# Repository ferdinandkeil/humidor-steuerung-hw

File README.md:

# Humidor Steuerung (Hardware)

Die aktuelle Version der Steuerung ist v35. Gefertigt wurden nur v31 und v35.

Wenn nicht anders angegeben stehen die Dateien unter der TAPR Open Hardware License (siehe LICENSE).

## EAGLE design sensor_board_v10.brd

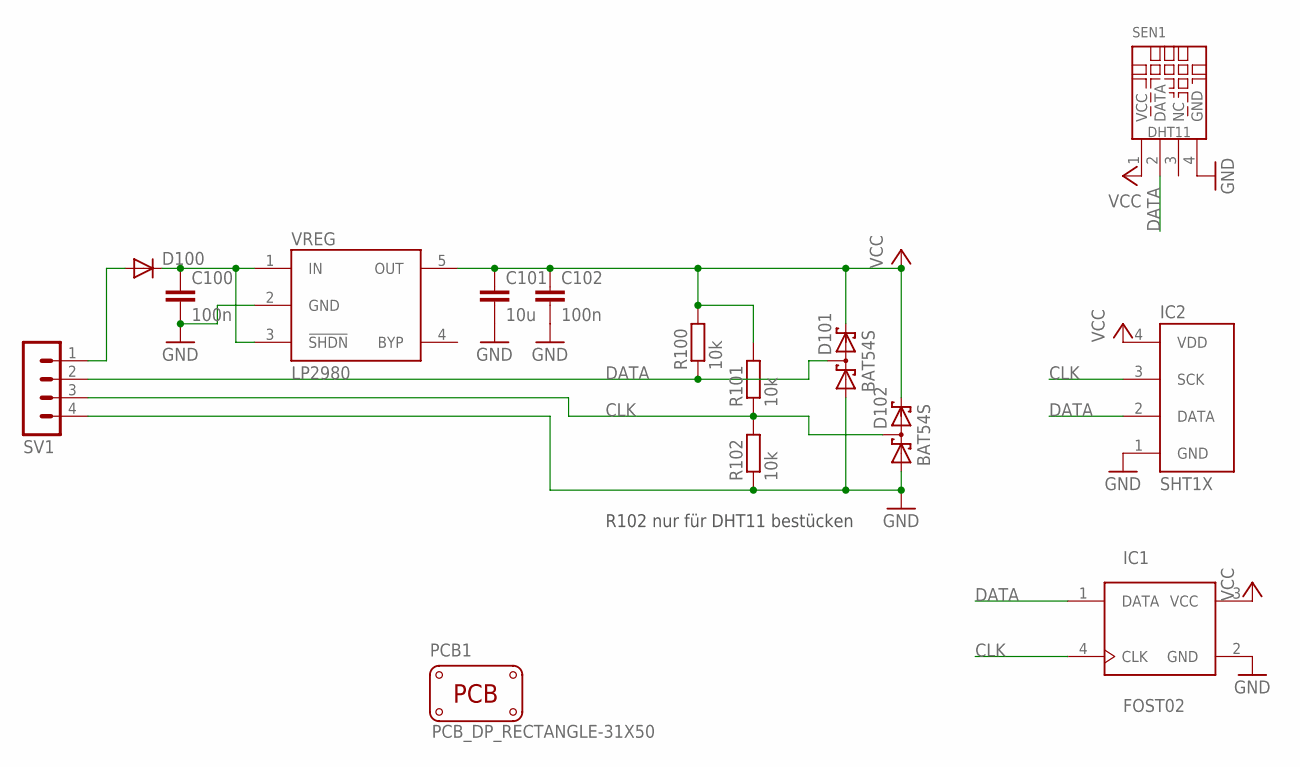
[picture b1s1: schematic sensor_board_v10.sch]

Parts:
C100, C102: 100n; C0805
C101: 10u; C0805
D100: DIODE-SOD123; SOD123
D101, D102: BAT54S; SOT23
IC1: FOST02
IC2: SHT1X
PCB1: PCB_DP_RECTANGLE-31X50; DP5031_V1
R100, R101, R102: 10k; R0805
SEN1: DHT11
SV1: MA04-1
VREG: LP2980; SOT-23-5

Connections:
CLK: D102.3 (C1A2), IC1.4 (CLK), IC2.3 (SCK), R101.1, R102.2, SV1.3
DATA: D101.3 (C1A2), IC1.1 (DATA), IC2.2 (DATA), R100.1, SEN1.2 (DATA), SV1.2
GND: C100.2, C101.2, C102.2, D101.1 (A1), D102.1 (A1), IC1.2 (GND), IC2.1 (GND), R102.1, SEN1.4 (GND), SV1.4, VREG.2 (GND)
unnamed: C100.1, D100.C, VREG.1 (IN), VREG.3 (!SHDN)
unnamed: D100.A, SV1.1
VCC: C101.1, C102.1, D101.2 (C2), D102.2 (C2), IC1.3 (VCC), IC2.4 (VDD), R100.2, R101.2, SEN1.1 (VCC), VREG.5 (OUT)

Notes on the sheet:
R102 nur für DHT11 bestücken

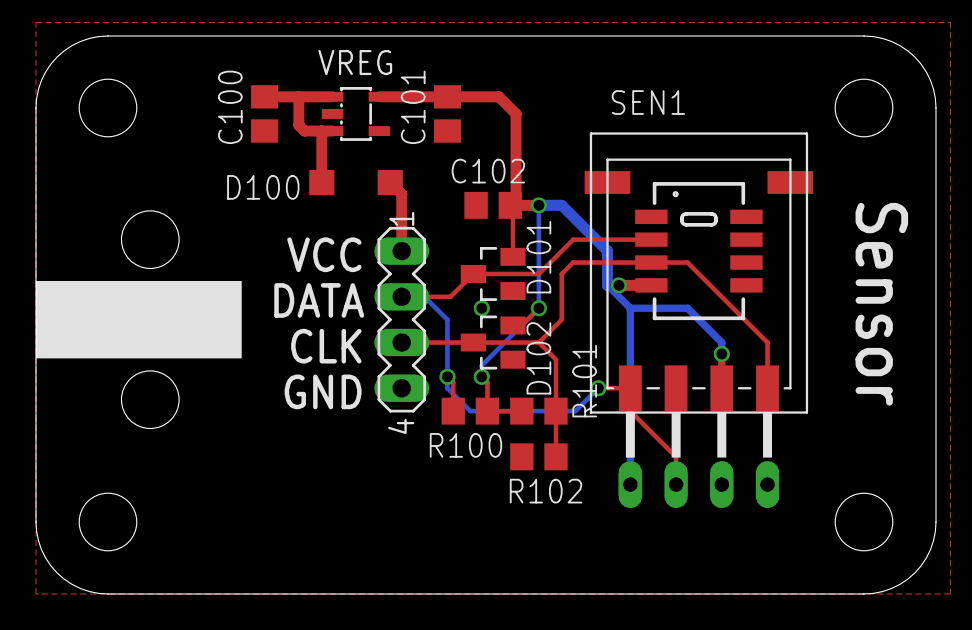
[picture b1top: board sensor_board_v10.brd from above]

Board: 2 copper layers, 50.0 x 31.0 mm, 16 parts (1 on the bottom side), 6 nets.

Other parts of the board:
U$1: ICON_LOGO_HUMI_CONTR

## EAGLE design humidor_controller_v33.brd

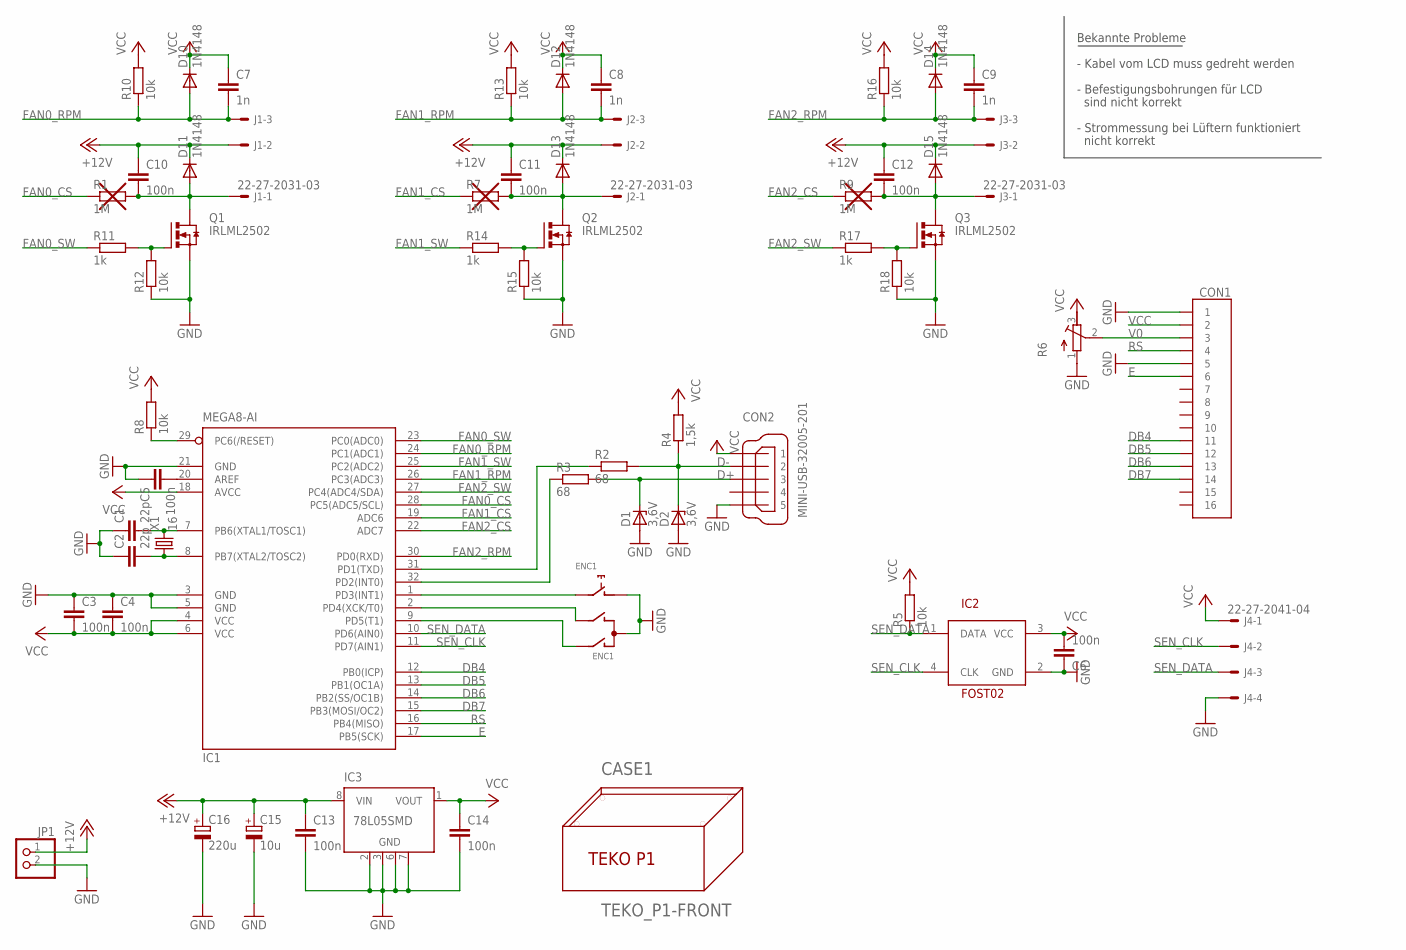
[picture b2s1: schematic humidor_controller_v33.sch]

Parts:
C1, C2: 22p; C0805
C3, C4, C5, C6, C10, C11, C12, C13, C14: 100n; C0805
C7, C8, C9: 1n; C0805
C15: 10u; PANASONIC_D
C16: 220u; PANASONIC_G
CASE1: TEKO_P1-FRONT; TEKO_P1_FRONT
CON1: 52207-16
CON2: MINI-USB-32005-201; 32005-201
D1, D2: 3,6V; SOD80C
D10, D11, D12, D13, D14, D15: 1N4148; SOD323-R
ENC1: NOBLE_RE0124; RE0124
IC1: MEGA8-AI; TQFP32-08
IC2: FOST02
IC3: 78L05SMD; SO08
J1, J2, J3: 22-27-2031-03; 6410-03
J4: 22-27-2041-04; 6410-04
JP1: PINHD-1X2; 1X02
Q1, Q2, Q3: IRLML2502; SOT23
R1, R7, R9: 1M; R0805
R2, R3: 68; R0805
R4: 1,5k; R0805
R5, R8, R10, R12, R13, R15, R16, R18: 10k; R0805
R6: R-TRIMM4G/J; RTRIM4G/J
R11, R14, R17: 1k; R0805
X1: 16; HC49UP

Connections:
+12V: C10.1, C11.1, C12.1, C13.1, C15.+, C16.+, D11.C, D13.C, D15.C, IC3.8 (VIN), J1.2, J2.2, J3.2, JP1.1
D+: CON2.3, D1.C, R3.2
D-: CON2.2, D2.C, R2.2, R4.1
DB4: CON1.11, IC1.12 (PB0(ICP))
DB5: CON1.12, IC1.13 (PB1(OC1A))
DB6: CON1.13, IC1.14 (PB2(SS/OC1B))
DB7: CON1.14, IC1.15 (PB3(MOSI/OC2))
E: CON1.6, IC1.17 (PB5(SCK))
FAN0_CS: IC1.28 (PC5(ADC5/SCL)), R1.1
FAN0_CS_: C10.2, D11.A, J1.1, Q1.3 (D), R1.2
FAN0_RPM: C7.2, D10.A, IC1.24 (PC1(ADC1)), J1.3, R10.1
FAN0_SW: IC1.23 (PC0(ADC0)), R11.1
FAN1_CS: IC1.19 (ADC6), R7.1
FAN1_CS_: C11.2, D13.A, J2.1, Q2.3 (D), R7.2
FAN1_RPM: C8.2, D12.A, IC1.26 (PC3(ADC3)), J2.3, R13.1
FAN1_SW: IC1.25 (PC2(ADC2)), R14.1
FAN2_CS: IC1.22 (ADC7), R9.1
FAN2_CS_: C12.2, D15.A, J3.1, Q3.3 (D), R9.2
FAN2_RPM: C9.2, D14.A, IC1.30 (PD0(RXD)), J3.3, R16.1
FAN2_SW: IC1.27 (PC4(ADC4/SDA)), R17.1
GND: C1.1, C2.1, C3.1, C4.1, C5.1, C6.1, C13.2, C14.2, C15.-, C16.-, CON1.1, CON1.5, CON2.5, D1.A, D2.A, ENC1.+ (1), ENC1.C, IC1.3 (GND), IC1.5 (GND), IC1.21 (GND), IC2.2 (GND), IC3.2 (GND), IC3.3 (GND), IC3.6 (GND), IC3.7 (GND), J4.4, JP1.2, Q1.2 (S), Q2.2 (S), Q3.2 (S), R6.1 (E), R12.1, R15.1, R18.1
unnamed: IC1.29 (PC6(/RESET)), R8.1
unnamed: C2.2, IC1.8 (PB7(XTAL2/TOSC2)), X1.1
unnamed: C1.2, IC1.7 (PB6(XTAL1/TOSC1)), X1.2
unnamed: Q2.1 (G), R14.2, R15.2
unnamed: Q3.1 (G), R17.2, R18.2
unnamed: C5.2, IC1.20 (AREF)
unnamed: Q1.1 (G), R11.2, R12.2
unnamed: IC1.31 (PD1(TXD)), R2.1
unnamed: ENC1.- (2), IC1.1 (PD3(INT1))
unnamed: ENC1.B, IC1.2 (PD4(XCK/T0))
unnamed: ENC1.A, IC1.9 (PD5(T1))
unnamed: IC1.32 (PD2(INT0)), R3.1
RS: CON1.4, IC1.16 (PB4(MISO))
SEN_CLK: IC1.11 (PD7(AIN1)), IC2.4 (CLK), J4.2
SEN_DATA: IC1.10 (PD6(AIN0)), IC2.1 (DATA), J4.3, R5.1
V0: CON1.3, R6.2 (S)
VCC: C3.2, C4.2, C6.2, C7.1, C8.1, C9.1, C14.1, CON1.2, CON2.1, D10.C, D12.C, D14.C, IC1.4 (VCC), IC1.6 (VCC), IC1.18 (AVCC), IC2.3 (VCC), IC3.1 (VOUT), J4.1, R4.2, R5.2, R6.3 (A), R8.2, R10.2, R13.2, R16.2

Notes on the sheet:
Bekannte Probleme
- Kabel vom LCD muss gedreht werden
- Befestigungsbohrungen für LCD
sind nicht korrekt
- Strommessung bei Lüftern funktioniert
nicht korrekt

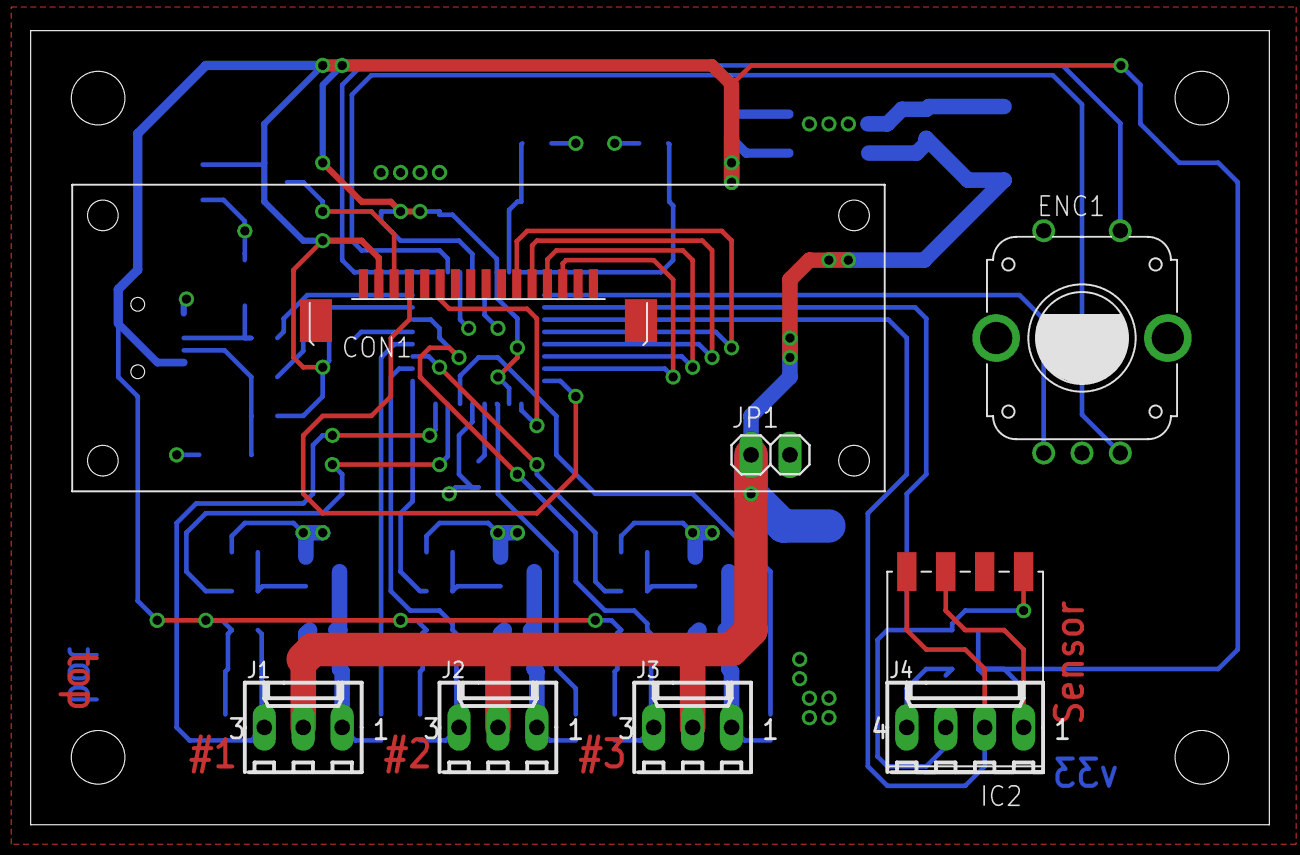
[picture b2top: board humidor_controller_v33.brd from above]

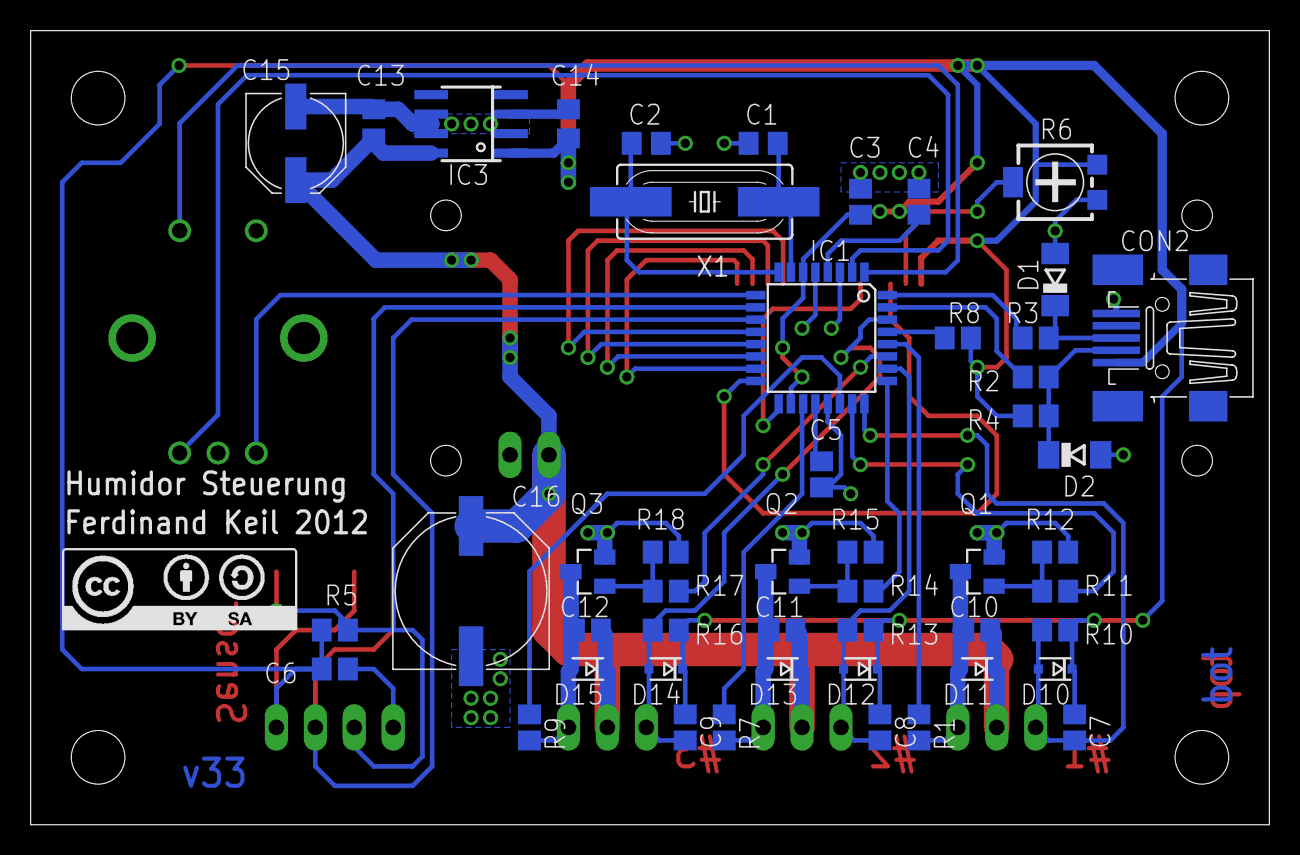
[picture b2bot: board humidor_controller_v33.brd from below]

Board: 2 copper layers, 80.8 x 51.8 mm, 60 parts (50 on the bottom side), 38 nets.

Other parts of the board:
U$1: LCD_HMC16223SG
U$2: CC-BY-SA

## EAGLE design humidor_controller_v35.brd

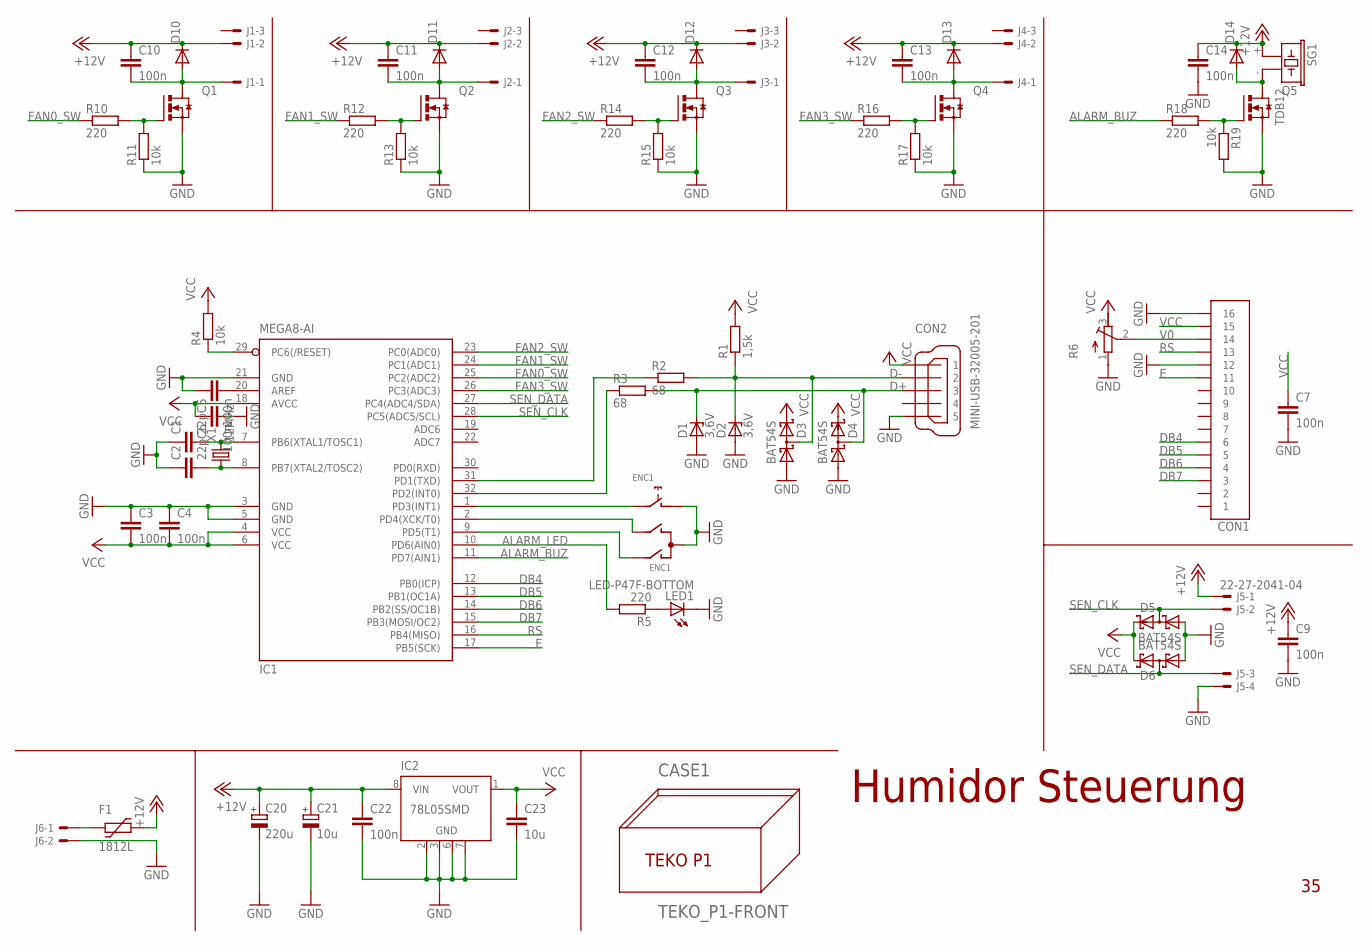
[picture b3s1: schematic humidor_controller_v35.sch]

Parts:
C1, C2: 22p; C0805
C3, C4, C5, C6, C7, C9, C10, C11, C12, C13, C14, C22: 100n; C0805
C20: 220u; PANASONIC_G
C21: 10u; PANASONIC_B
C23: 10u; C0805
CASE1: TEKO_P1-FRONT; TEKO_P1_FRONT
CON1: 52207-16
CON2: MINI-USB-32005-201; 32005-201
D1, D2: 3,6V; SOD80C
D3, D4, D5, D6: BAT54S; SOT23
D10, D11, D12, D13, D14: DIODE-SOD123; SOD123
ENC1: NOBLE_RE0124; RE0124
F1: 1812L
IC1: MEGA8-AI; TQFP32-08
IC2: 78L05SMD; SO08
J1, J2, J3, J4: 22-27-2031-03; 6410-03
J5: 22-27-2041-04; 6410-04
J6: 22-27-2021-02; 6410-02
LED1: LED-P47F-BOTTOM; P47F-BOTTOM
Q1, Q2, Q3, Q4, Q5: N-HEXFET_SOT23-IRLML2502; SOT23
R1: 1,5k; R0805
R2, R3: 68; R0805
R4, R11, R13, R15, R17, R19: 10k; R0805
R5, R10, R12, R14, R16, R18: 220; R0805
R6: R-TRIMM4G/J; RTRIM4G/J
SG1: TDB12; TDB
X1: 12MHz; HC49UP

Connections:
+12V: C9.1, C10.1, C11.1, C12.1, C13.1, C14.1, C20.+, C21.+, C22.1, D10.C, D11.C, D12.C, D13.C, D14.C, F1.P$2 (2), IC2.8 (VIN), J1.2, J2.2, J3.2, J4.2, J5.1, SG1.+ (1)
ALARM_BUZ: IC1.11 (PD7(AIN1)), R18.1
ALARM_LED: IC1.10 (PD6(AIN0)), R5.2
D+: CON2.3, D1.C, D4.3 (C1A2), R3.2
D-: CON2.2, D2.C, D3.3 (C1A2), R1.1, R2.2
DB4: CON1.6, IC1.12 (PB0(ICP))
DB5: CON1.5, IC1.13 (PB1(OC1A))
DB6: CON1.4, IC1.14 (PB2(SS/OC1B))
DB7: CON1.3, IC1.15 (PB3(MOSI/OC2))
E: CON1.11, IC1.17 (PB5(SCK))
FAN0_CS: C10.2, D10.A, J1.1, Q1.3 (D)
FAN0_SW: IC1.25 (PC2(ADC2)), R10.1
FAN1_CS: C11.2, D11.A, J2.1, Q2.3 (D)
FAN1_SW: IC1.24 (PC1(ADC1)), R12.1
FAN2_CS: C12.2, D12.A, J3.1, Q3.3 (D)
FAN2_CS1: C13.2, D13.A, J4.1, Q4.3 (D)
FAN2_SW: IC1.23 (PC0(ADC0)), R14.1
FAN3_SW: IC1.26 (PC3(ADC3)), R16.1
GND: C1.1, C2.1, C3.1, C4.1, C5.1, C6.2, C7.2, C9.2, C14.2, C20.-, C21.-, C22.2, C23.2, CON1.12, CON1.16, CON2.5, D1.A, D2.A, D3.1 (A1), D4.1 (A1), D5.1 (A1), D6.1 (A1), ENC1.+ (1), ENC1.C, IC1.3 (GND), IC1.5 (GND), IC1.21 (GND), IC2.2 (GND), IC2.3 (GND), IC2.6 (GND), IC2.7 (GND), J5.4, J6.2, LED1.C, Q1.2 (S), Q2.2 (S), Q3.2 (S), Q4.2 (S), Q5.2 (S), R6.1 (E), R11.1, R13.1, R15.1, R17.1, R19.2
unnamed: IC1.29 (PC6(/RESET)), R4.1
unnamed: C2.2, IC1.8 (PB7(XTAL2/TOSC2)), X1.1
unnamed: C1.2, IC1.7 (PB6(XTAL1/TOSC1)), X1.2
unnamed: Q2.1 (G), R12.2, R13.2
unnamed: Q3.1 (G), R14.2, R15.2
unnamed: Q4.1 (G), R16.2, R17.2
unnamed: C5.2, IC1.20 (AREF)
unnamed: LED1.A, R5.1
unnamed: Q1.1 (G), R10.2, R11.2
unnamed: IC1.31 (PD1(TXD)), R2.1
unnamed: F1.P$1 (1), J6.1
unnamed: ENC1.- (2), IC1.1 (PD3(INT1))
unnamed: ENC1.B, IC1.2 (PD4(XCK/T0))
unnamed: ENC1.A, IC1.9 (PD5(T1))
unnamed: IC1.32 (PD2(INT0)), R3.1
unnamed: D14.A, Q5.3 (D), SG1.- (2)
unnamed: Q5.1 (G), R18.2, R19.1
RS: CON1.13, IC1.16 (PB4(MISO))
SEN_CLK: D5.3 (C1A2), IC1.28 (PC5(ADC5/SCL)), J5.2
SEN_DATA: D6.3 (C1A2), IC1.27 (PC4(ADC4/SDA)), J5.3
V0: CON1.14, R6.2 (S)
VCC: C3.2, C4.2, C6.1, C7.1, C23.1, CON1.15, CON2.1, D3.2 (C2), D4.2 (C2), D5.2 (C2), D6.2 (C2), IC1.4 (VCC), IC1.6 (VCC), IC1.18 (AVCC), IC2.1 (VOUT), R1.2, R4.2, R6.3 (A)

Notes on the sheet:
Humidor Steuerung

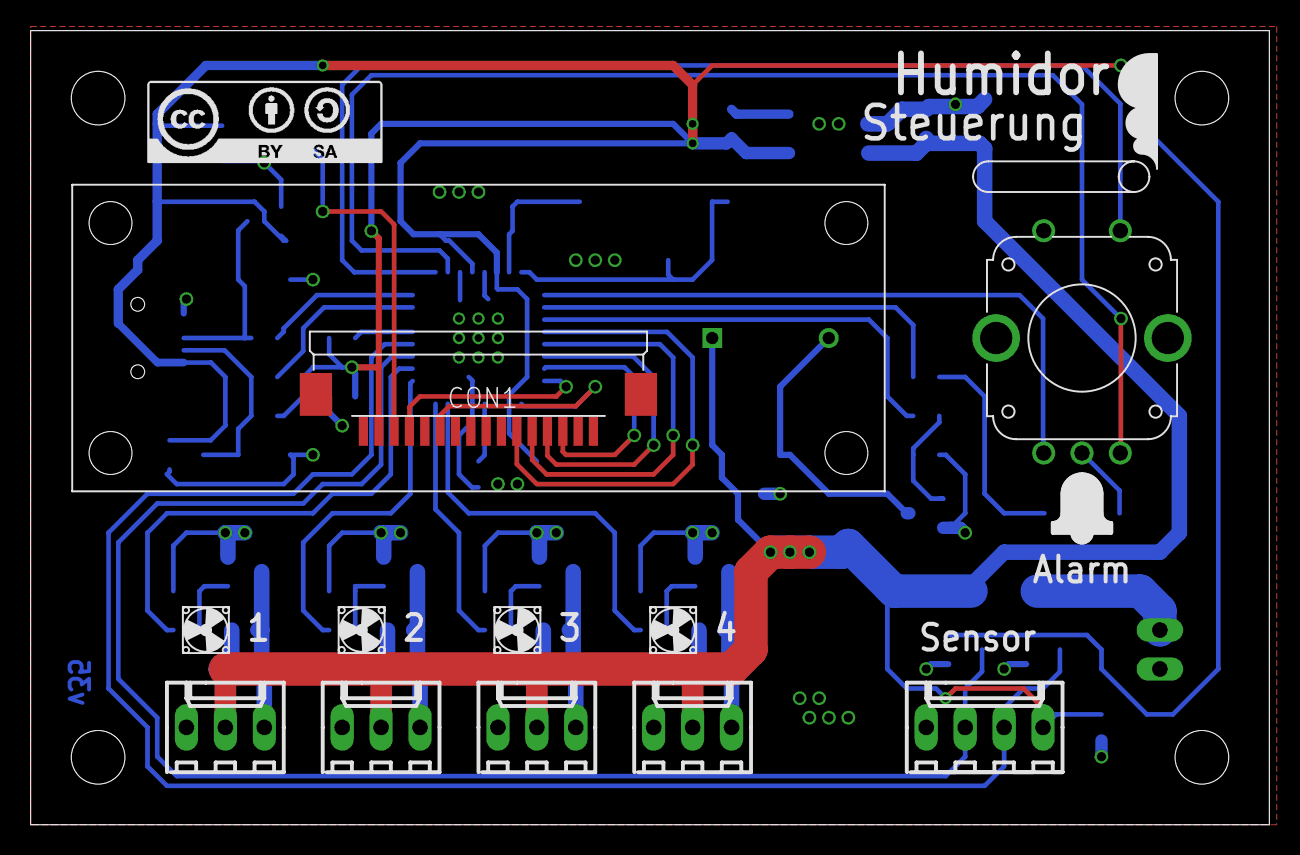
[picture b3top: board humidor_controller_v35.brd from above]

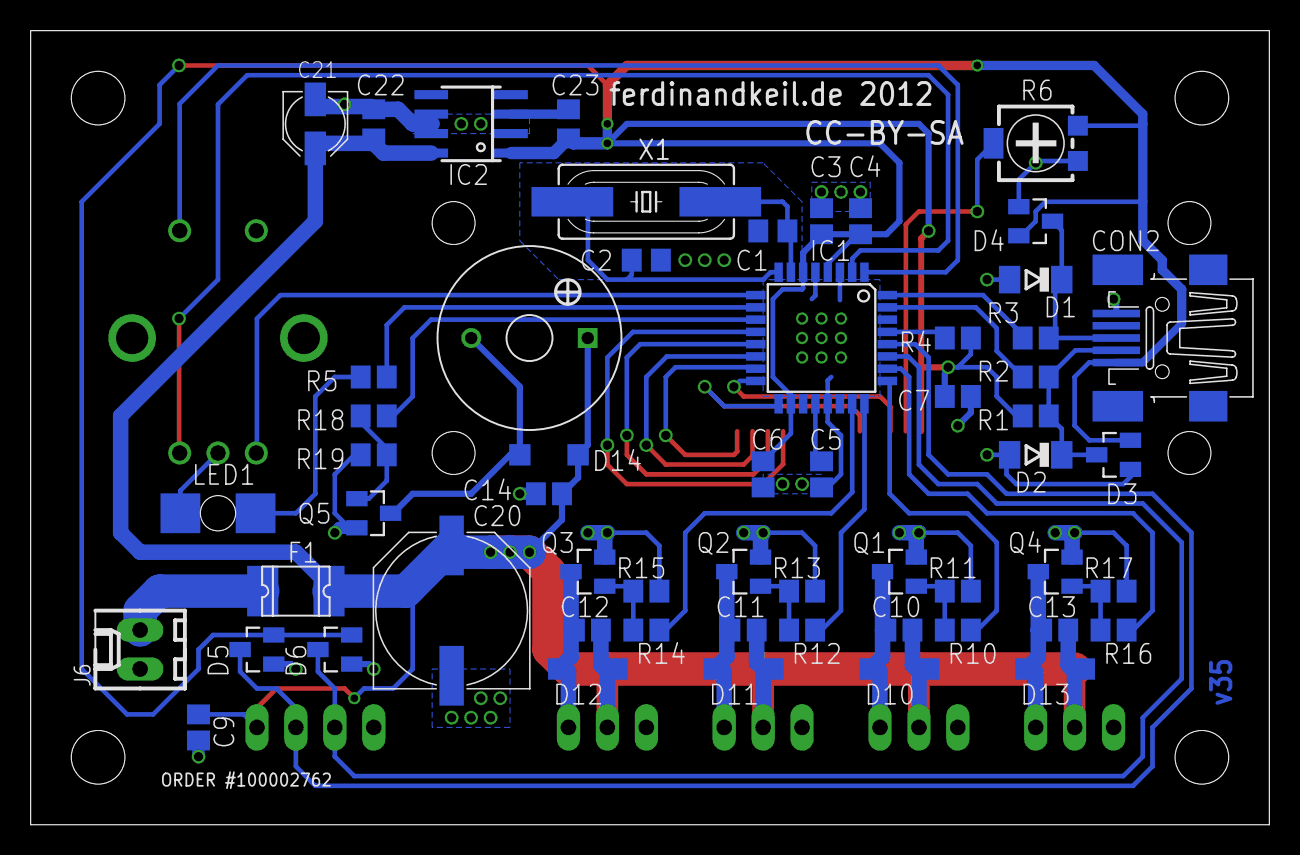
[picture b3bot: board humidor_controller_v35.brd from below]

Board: 2 copper layers, 80.8 x 51.8 mm, 72 parts (57 on the bottom side), 41 nets.

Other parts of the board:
U$1: LCD_HMC16223SG
U$2: CC-BY-SA
U$3: ICON_LOGO_HUMI_CONTR
U$4, U$5, U$6, U$7: ICON_FAN_3X3MM

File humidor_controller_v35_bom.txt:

Partlist

Exported from humidor_controller_v35.sch at 24.09.2012 16:11:15

EAGLE Version 6.2.0 Copyright (c) 1988-2012 CadSoft

Assembly variant: 

Part     Value                    Device                   Package     Library               Sheet

C1       22p                      C-EUC0805                C0805       rcl                   1
C2       22p                      C-EUC0805                C0805       rcl                   1
C3       100n                     C-EUC0805                C0805       resistor              1
C4       100n                     C-EUC0805                C0805       resistor              1
C5       100n                     C-EUC0805                C0805       resistor              1
C6       100n                     C-EUC0805                C0805       resistor              1
C7       100n                     C-EUC0805                C0805       resistor              1
C9       100n                     C-EUC0805                C0805       resistor              1
C10      100n                     C-EUC0805                C0805       resistor              1
C11      100n                     C-EUC0805                C0805       resistor              1
C12      100n                     C-EUC0805                C0805       resistor              1
C13      100n                     C-EUC0805                C0805       resistor              1
C14      100n                     C-EUC0805                C0805       resistor              1
C20      220u                     CPOL-EUG                 PANASONIC_G rcl                   1
C21      10u                      CPOL-EUB                 PANASONIC_B rcl                   1
C22      100n                     C-EUC0805                C0805       rcl                   1
C23      10u                      C-EUC0805                C0805       rcl                   1
CON1                              52207-16                 52207-16    jt-con-molex          1
CON2     MINI-USB-32005-201       MINI-USB-32005-201       32005-201   con-cypressindustries 1
D1       3,6V                     ZENER-DIODESOD80C        SOD80C      diode                 1
D2       3,6V                     ZENER-DIODESOD80C        SOD80C      diode                 1
D3       BAT54S                   BAT54S                   SOT23       diode                 1
D4       BAT54S                   BAT54S                   SOT23       diode                 1
D5       BAT54S                   BAT54S                   SOT23       diode                 1
D6       BAT54S                   BAT54S                   SOT23       diode                 1
D10                               DIODE-SOD123             SOD123      ferdinandkeil         1
D11                               DIODE-SOD123             SOD123      ferdinandkeil         1
D12                               DIODE-SOD123             SOD123      ferdinandkeil         1
D13                               DIODE-SOD123             SOD123      ferdinandkeil         1
D14                               DIODE-SOD123             SOD123      ferdinandkeil         1
ENC1                              NOBLE_RE0124             RE0124      ferdinandkeil         1
F1       1812L                    1812L                    1812L       ptc-littlefuse        1
IC1      MEGA8-AI                 MEGA8-AI                 TQFP32-08   atmel                 1
IC3      78L05SMD                 78L05SMD                 SO08        linear                1
J1       22-27-2031-03            22-27-2031-03            6410-03     ferdinandkeil         1
J2       22-27-2031-03            22-27-2031-03            6410-03     ferdinandkeil         1
J3       22-27-2031-03            22-27-2031-03            6410-03     ferdinandkeil         1
J4       22-27-2041-04            22-27-2041-04            6410-04     ferdinandkeil         1
J5       22-27-2021-02            22-27-2021-02            6410-02     ferdinandkeil         1
J6       22-27-2031-03            22-27-2031-03            6410-03     ferdinandkeil         1
LED1     LED-P47F-BOTTOM          LED-P47F-BOTTOM          P47F-BOTTOM ferdinandkeil         1
Q1       N-HEXFET_SOT23-IRLML2502 N-HEXFET_SOT23-IRLML2502 SOT23       ferdinandkeil         1
Q2       N-HEXFET_SOT23-IRLML2502 N-HEXFET_SOT23-IRLML2502 SOT23       ferdinandkeil         1
Q3       N-HEXFET_SOT23-IRLML2502 N-HEXFET_SOT23-IRLML2502 SOT23       ferdinandkeil         1
Q4       N-HEXFET_SOT23-IRLML2502 N-HEXFET_SOT23-IRLML2502 SOT23       ferdinandkeil         1
Q5       N-HEXFET_SOT23-IRLML2502 N-HEXFET_SOT23-IRLML2502 SOT23       ferdinandkeil         1
R1       1,5k                     R-EU_R0805               R0805       resistor              1
R2       68                       R-EU_R0805               R0805       resistor              1
R3       68                       R-EU_R0805               R0805       resistor              1
R4       10k                      R-EU_R0805               R0805       resistor              1
R5       220                      R-EU_R0805               R0805       resistor              1
R6                                R-TRIMM4G/J              RTRIM4G/J   rcl                   1
R10      220                      R-EU_R0805               R0805       resistor              1
R11      10k                      R-EU_R0805               R0805       resistor              1
R12      220                      R-EU_R0805               R0805       resistor              1
R13      10k                      R-EU_R0805               R0805       resistor              1
R14      220                      R-EU_R0805               R0805       resistor              1
R15      10k                      R-EU_R0805               R0805       resistor              1
R16      220                      R-EU_R0805               R0805       resistor              1
R17      10k                      R-EU_R0805               R0805       resistor              1
R18      220                      R-EU_R0805               R0805       resistor              1
R19      10k                      R-EU_R0805               R0805       resistor              1
SG1      TDB12                    TDB12                    TDB         ferdinandkeil         1
X1       16                       CRYSTALHC49UP            HC49UP      crystal               1

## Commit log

2012-12-13 Initial import
2012-12-15 Added README.md and LICENSE
